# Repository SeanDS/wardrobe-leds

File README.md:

# Wardrobe light sensor/driver
This circuit allows for four independent light sensors and LED drivers. It can
be used to sense if a wardrobe (or any door) is opened and trigger an LED strip
to come on. It allows sensitivity of the LDR to be tuned using trimmers.

## Credits
Sean Leavey  
https://github.com/SeanDS

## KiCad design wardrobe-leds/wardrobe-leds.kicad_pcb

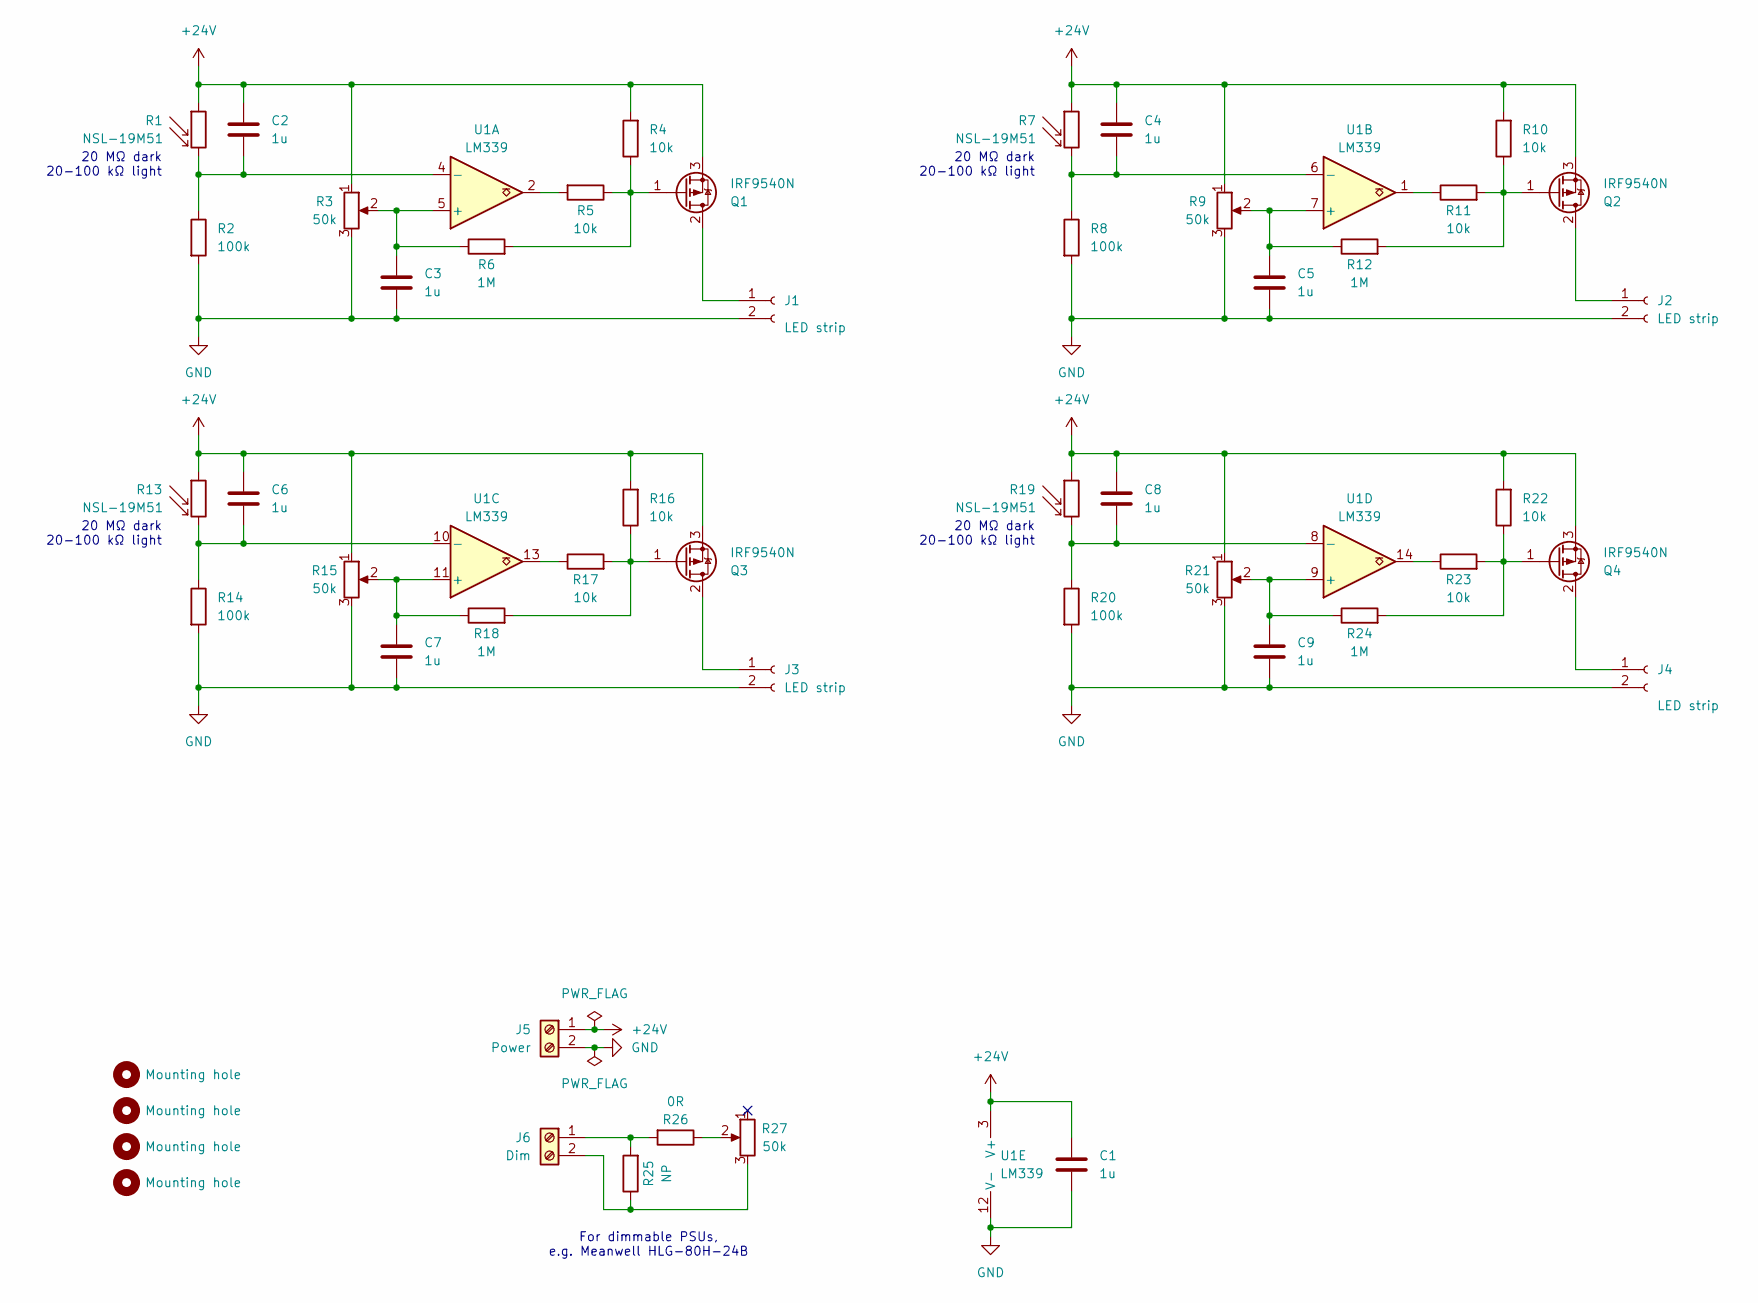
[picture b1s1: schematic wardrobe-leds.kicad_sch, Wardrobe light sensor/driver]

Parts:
C1, C2, C3, C4, C5, C6, C7, C8, C9: 1u; C_0805_2012Metric
H1, H2, H3, H4: Mounting hole; MountingHole_3.2mm_M3
J1, J2, J3, J4: LED strip; Molex_Nano-Fit_105313-xx02_1x02_P2.50mm_Horizontal
J5: Power; TerminalBlock_Phoenix_MKDS-3-2-5.08_1x02_P5.08mm_Horizontal
J6: Dim; TerminalBlock_Phoenix_MKDS-3-2-5.08_1x02_P5.08mm_Horizontal
Q1, Q2, Q3, Q4: IRF9540N; TO-220-3_Horizontal_TabDown
R1, R7, R13, R19: NSL-19M51; Molex_Nano-Fit_105313-xx02_1x02_P2.50mm_Horizontal
R2, R8, R14, R20: 100k; R_0805_2012Metric
R3, R9, R15, R21, R27: 50k; Potentiometer_Bourns_3314J_Vertical; MPN1 3314G-2-503E
R4, R5, R10, R11, R16, R17, R22, R23: 10k; R_0805_2012Metric
R6, R12, R18, R24: 1M; R_0805_2012Metric
R25: NP; R_0805_2012Metric
R26: 0R; R_0805_2012Metric
U1: LM339; SOIC-14_3.9x8.7mm_P1.27mm; MPN1 LM339D

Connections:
+24V: C1.1, C2.1, C4.1, C6.1, C8.1, J5.1, Q1.3 (S), Q2.3 (S), Q3.3 (S), Q4.3 (S), R1.1, R3.1, R4.2, R7.1, R9.1, R10.2, R13.1, R15.1, R16.2, R19.1, R21.1, R22.2, U1.3 (V+)
GND: C1.2, C3.2, C5.2, C7.2, C9.2, J1.2, J2.2, J3.2, J4.2, J5.2, R2.2, R3.3, R8.2, R9.3, R14.2, R15.3, R20.2, R21.3, U1.12 (V-)
unnamed: J1.1, Q1.2 (D)
unnamed: J2.1, Q2.2 (D)
unnamed: J3.1, Q3.2 (D)
unnamed: J4.1, Q4.2 (D)
unnamed: J6.1, R25.2, R26.2
unnamed: J6.2, R25.1, R27.3
unnamed: Q1.1 (G), R4.1, R5.1, R6.2
unnamed: Q2.1 (G), R10.1, R11.2, R12.2
unnamed: Q3.1 (G), R16.1, R17.2, R18.2
unnamed: Q4.1 (G), R22.1, R23.2, R24.2
unnamed: R5.2, U1.2
unnamed: R11.1, U1.1
unnamed: R17.1, U1.13
unnamed: R23.1, U1.14
unnamed: R26.1, R27.2
unnamed: C3.1, R3.2, R6.1, U1.5 (+)
unnamed: C2.2, R1.2, R2.1, U1.4 (-)
unnamed: C5.1, R9.2, R12.1, U1.7 (+)
unnamed: C4.2, R7.2, R8.1, U1.6 (-)
unnamed: C7.1, R15.2, R18.1, U1.11 (+)
unnamed: C6.2, R13.2, R14.1, U1.10 (-)
unnamed: C9.1, R21.2, R24.1, U1.9 (+)
unnamed: C8.2, R19.2, R20.1, U1.8 (-)

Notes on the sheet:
20 MΩ dark 20-100 kΩ light
For dimmable PSUs, e.g. Meanwell HLG-80H-24B

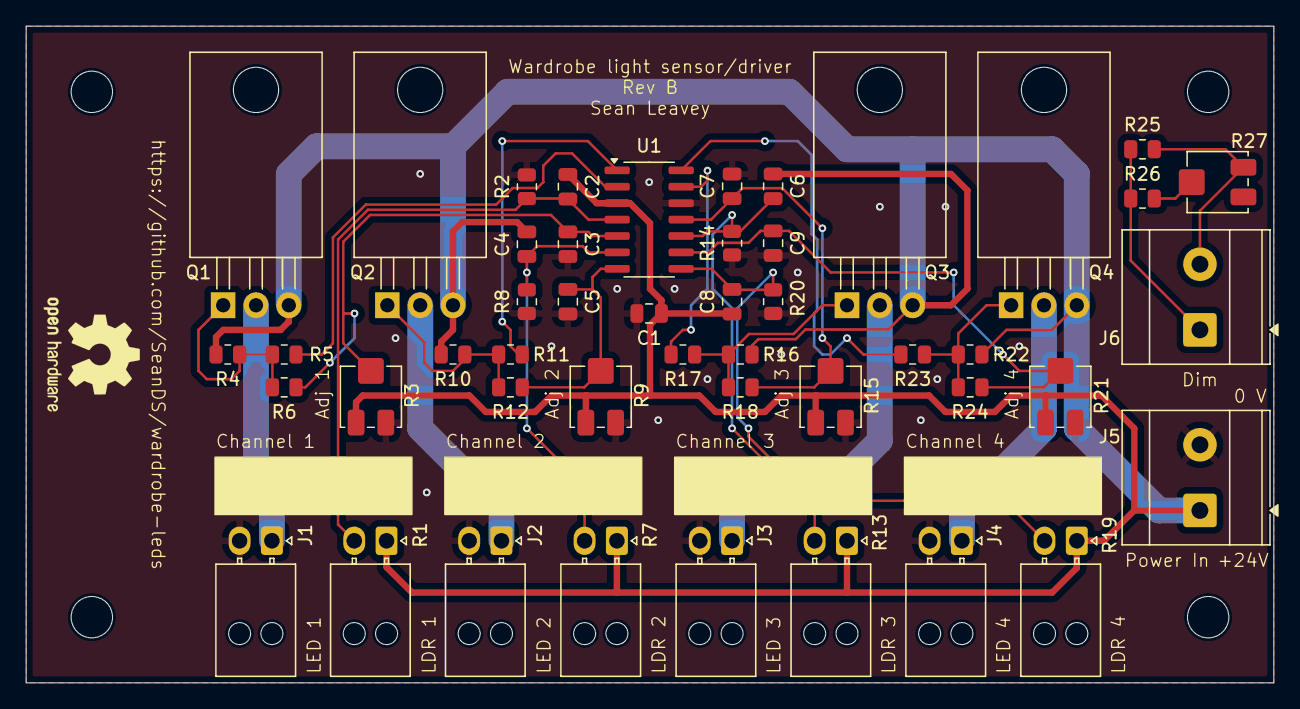
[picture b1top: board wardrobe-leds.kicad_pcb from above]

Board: 2 copper layers, 96.5 x 50.8 mm, 51 parts (0 on the bottom side), 25 nets.

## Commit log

2025-08-01 Add licence
2025-08-01 Add first design
2025-08-16 Update driver to use P-channel MOSFET to avoid Vgs voltage drop; add dimmer control; add hysteresis
